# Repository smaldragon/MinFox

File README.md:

# MinFox

**NOTE: As of now, the board is untested, this README will be updated once proper tests with the physical board have taken place**

This is a minimal 65c02 board for prototyping, it provides ROM, RAM, 6 Chip Select lines (S1-S6), and a large jumper header with all the required signals to connect to daughter boards or to breadboards. The goal is to have a dumb, as simple as possible board for testing peripherals connected to a 65c02 bus.

All components are through hole, as to allow for an easier soldering experience and for the installation of sockets for IC reuse.

## Bill of Materials

* wdc65c02 CPU (dip-40)
* 74hc00 Quad Nand Gate (dip-14)
* 74hc138 3-to-8 Decoder (dip-16)
* Standard 62xxx SRAM (dip-28 or dip-32)
* Standard 28cXX EEPROM (dip-28) or 39SF0x0 Flash NOR (dip-32 or PLCC-32)
* Standard 1Mhz Clock Oscillator

* 2x20 Pin Socket (same size as RPi connector)
* 1x3  Pin Socket
* 2x2  Pin Header (+ 2 Jumpers)
* DIP-12 Switch
* Small 6-Pin Power Slide Switch
* USB-B Connector (power)

* 3xPush Buttons
* 1x470Ω
* 3x1KΩ
* 1x10µF Polarized Capacitor
* 8x0.1µF Capacitor
* 2x9pin Resistor Networks

The location and values of all components are also described in the board silk screen.

## Change Log

Board revisions  follow a `v$number$letter` naming scheme, the number symbolizes a board with new features and incompatibilities, while the letter symbolizes fixes and minor tweaks. The current version is **v1a**

### v1a

* Fixed breaking bug with /WR signal
* Added Screw Mounts
* Added Support for DIP-32 RAM and DIP-32/PLCC-32 Flash NOR chips
* Added Jumper for disconnecting clock oscillator
* Added Jumper for gating slot select signals with ø2
* Added dip switch for setting a ROM bank to use
* Added Set Overflow signal to the Connector
* Changed footprint of power slide switch
* Many tweaks to silkscreen

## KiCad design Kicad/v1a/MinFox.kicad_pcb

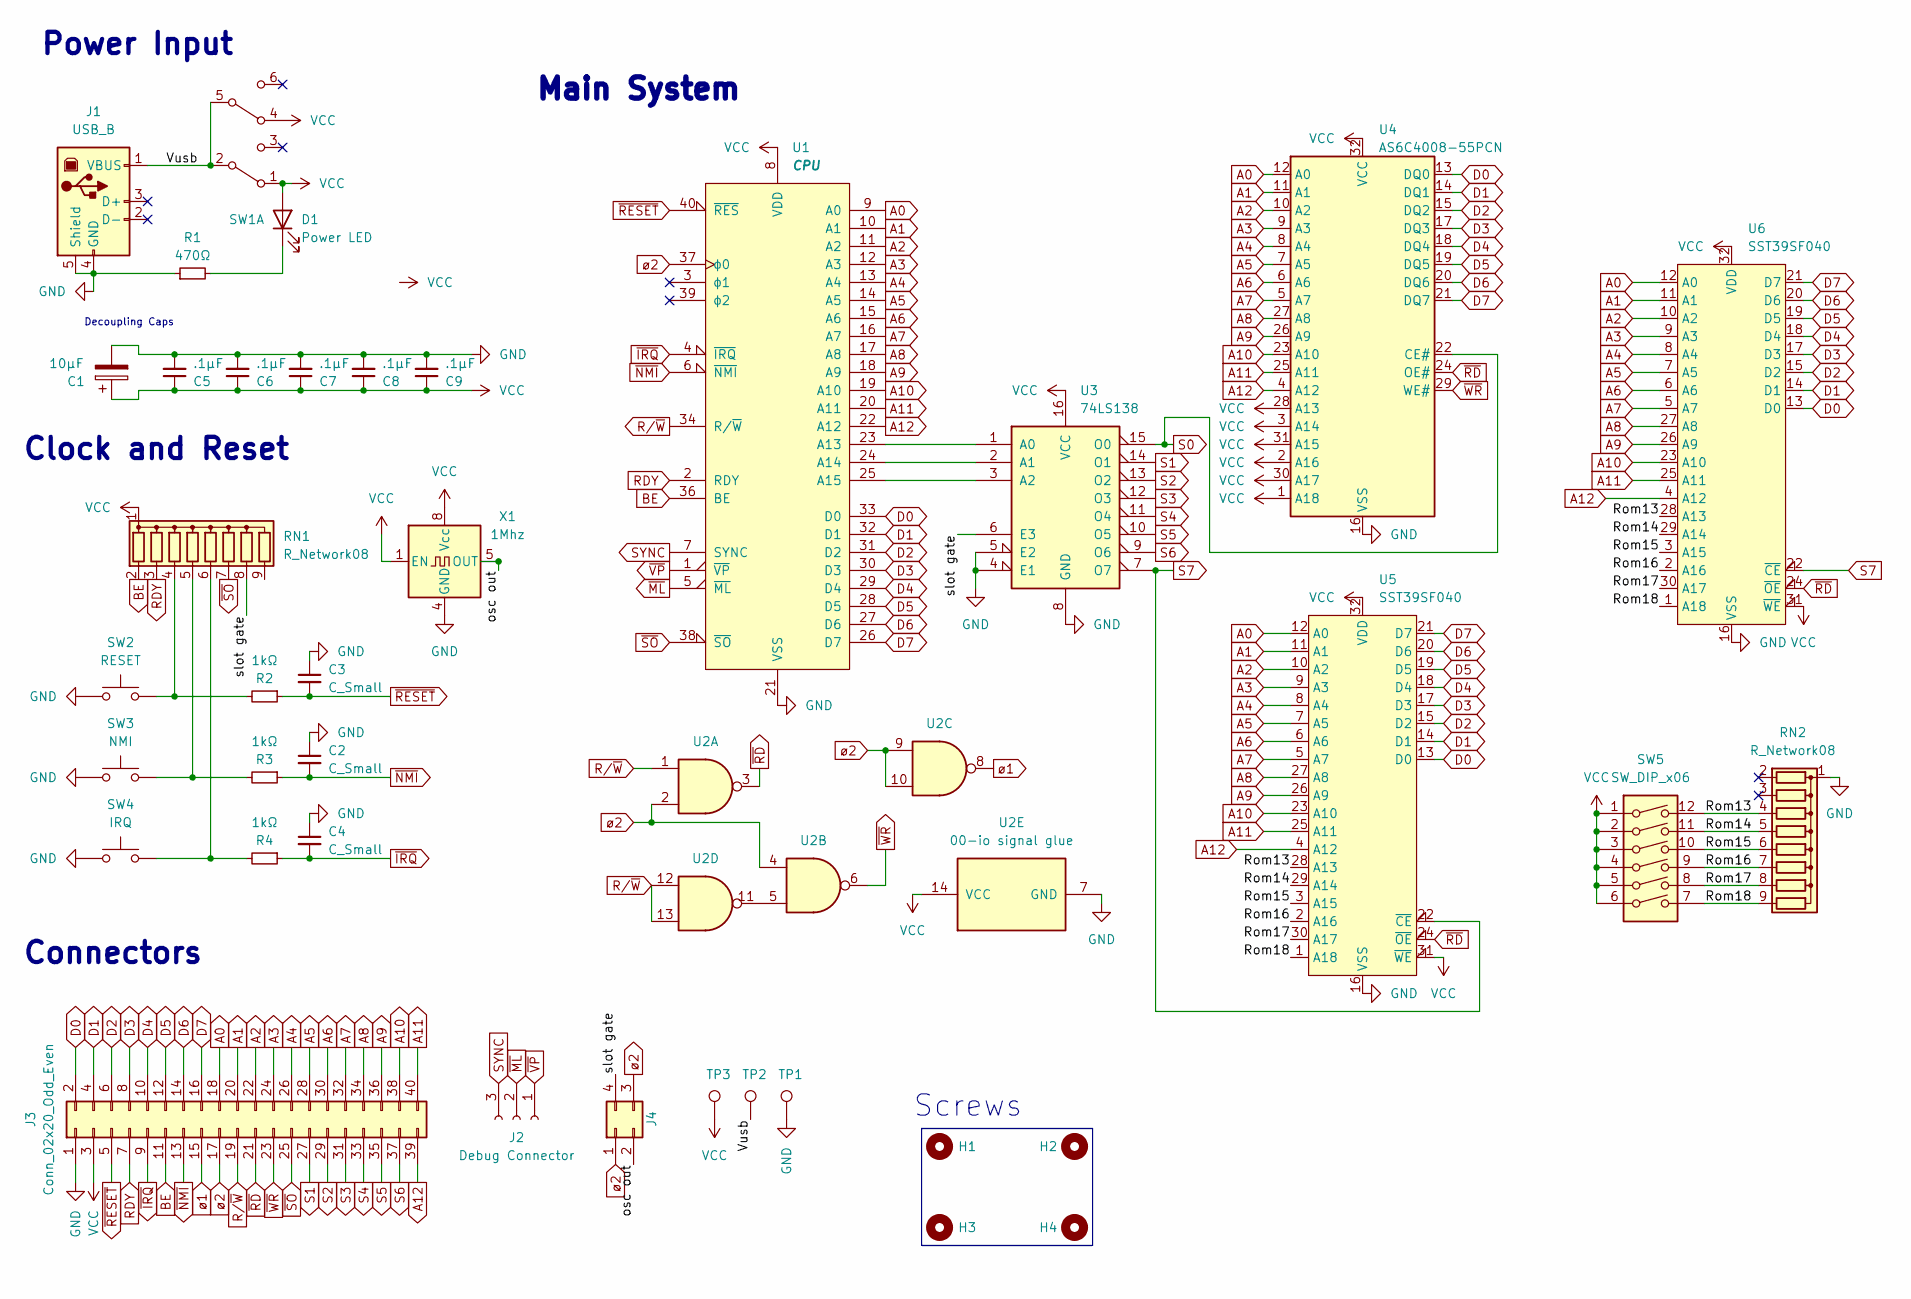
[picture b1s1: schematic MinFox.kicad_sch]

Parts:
C1: 10µF; CP_Radial_D4.0mm_P1.50mm
C2, C3, C4: C_Small; C_Disc_D3.0mm_W1.6mm_P2.50mm
C5, C6, C7, C8, C9: .1µF; C_Disc_D3.0mm_W1.6mm_P2.50mm
D1: Power LED; LED_D5.0mm
H1, H2, H3, H4: MountingHole; MountingHole_3.2mm_M3
J1: USB_B; USB_B_OST_USB-B1HSxx_Horizontal
J2: Debug Connector; PinSocket_1x03_P2.54mm_Vertical
J3: Conn_02x20_Odd_Even; PinSocket_2x20_P2.54mm_Vertical
J4: Conn_02x02_Counter_Clockwise; PinHeader_2x02_P2.54mm_Vertical
R1: 470Ω; R_Axial_DIN0204_L3.6mm_D1.6mm_P7.62mm_Horizontal
R2, R3, R4: 1kΩ; R_Axial_DIN0204_L3.6mm_D1.6mm_P7.62mm_Horizontal
RN1, RN2: R_Network08; R_Array_SIP9
SW1: SW_DPDT_x2; SW_CuK_JS202011AQN_DPDT_Angled
SW2: RESET; SW_PUSH_6mm
SW3: NMI; SW_PUSH_6mm
SW4: IRQ; SW_PUSH_6mm
SW5: SW_DIP_x06; SW_DIP_SPSTx06_Slide_6.7x16.8mm_W7.62mm_P2.54mm_LowProfile
TP1: GND; TestPoint_Pad_D2.0mm
TP2: Vusb; TestPoint_Pad_D2.0mm
TP3: Vcc; TestPoint_Pad_D2.0mm
U1: CPU; DIP-40_W15.24mm_Socket
U2: 00-io signal glue; DIP-14_W7.62mm_Socket
U3: 74LS138; DIP-16_W7.62mm_Socket
U4: AS6C4008-55PCN; DIP-32_W15.24mm_Socket
U5: SST39SF040; DIP-32_W15.24mm_Socket
U6: SST39SF040; PLCC-32_THT-Socket
X1: 1Mhz; Oscillator_DIP-8

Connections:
/Rom13: RN2.4 (R3), SW5.12, U5.28 (A13), U6.28 (A13)
/Rom14: RN2.5 (R4), SW5.11, U5.29 (A14), U6.29 (A14)
/Rom15: RN2.6 (R5), SW5.10, U5.3 (A15), U6.3 (A15)
/Rom16: RN2.7 (R6), SW5.9, U5.2 (A16), U6.2 (A16)
/Rom17: RN2.8 (R7), SW5.8, U5.30 (A17), U6.30 (A17)
/Rom18: RN2.9 (R8), SW5.7, U5.1 (A18), U6.1 (A18)
/Vusb: J1.1 (VBUS), SW1.2 (B), SW1.5 (B), TP2.1
/osc out: J4.2, X1.5 (OUT)
/slot gate: J4.4, RN1.8 (R7), U3.6 (E3)
A0: J3.18, U1.9 (A0), U4.12 (A0), U5.12 (A0), U6.12 (A0)
A1: J3.20, U1.10 (A1), U4.11 (A1), U5.11 (A1), U6.11 (A1)
A2: J3.22, U1.11 (A2), U4.10 (A2), U5.10 (A2), U6.10 (A2)
A3: J3.24, U1.12 (A3), U4.9 (A3), U5.9 (A3), U6.9 (A3)
A4: J3.26, U1.13 (A4), U4.8 (A4), U5.8 (A4), U6.8 (A4)
A5: J3.28, U1.14 (A5), U4.7 (A5), U5.7 (A5), U6.7 (A5)
A6: J3.30, U1.15 (A6), U4.6 (A6), U5.6 (A6), U6.6 (A6)
A7: J3.32, U1.16 (A7), U4.5 (A7), U5.5 (A7), U6.5 (A7)
A8: J3.34, U1.17 (A8), U4.27 (A8), U5.27 (A8), U6.27 (A8)
A9: J3.36, U1.18 (A9), U4.26 (A9), U5.26 (A9), U6.26 (A9)
A10: J3.38, U1.19 (A10), U4.23 (A10), U5.23 (A10), U6.23 (A10)
A11: J3.40, U1.20 (A11), U4.25 (A11), U5.25 (A11), U6.25 (A11)
A12: J3.39, U1.22 (A12), U4.4 (A12), U5.4 (A12), U6.4 (A12)
BE: J3.11, RN1.2 (R1), U1.36 (BE)
D0: J3.2, U1.33 (D0), U4.13 (DQ0), U5.13 (D0), U6.13 (D0)
D1: J3.4, U1.32 (D1), U4.14 (DQ1), U5.14 (D1), U6.14 (D1)
D2: J3.6, U1.31 (D2), U4.15 (DQ2), U5.15 (D2), U6.15 (D2)
D3: J3.8, U1.30 (D3), U4.17 (DQ3), U5.17 (D3), U6.17 (D3)
D4: J3.10, U1.29 (D4), U4.18 (DQ4), U5.18 (D4), U6.18 (D4)
D5: J3.12, U1.28 (D5), U4.19 (DQ5), U5.19 (D5), U6.19 (D5)
D6: J3.14, U1.27 (D6), U4.20 (DQ6), U5.20 (D6), U6.20 (D6)
D7: J3.16, U1.26 (D7), U4.21 (DQ7), U5.21 (D7), U6.21 (D7)
GND: C1.2, C2.1, C3.1, C4.1, C5.2, C6.2, C7.2, C8.2, C9.2, J1.4 (GND), J1.5 (Shield), J3.1, R1.1, RN2.1 (common), SW2.1, SW3.1, SW4.1, TP1.1, U1.21 (VSS), U2.7 (GND), U3.4 (E1), U3.5 (E2), U3.8 (GND), U4.16 (VSS), U5.16 (VSS), U6.16 (VSS), X1.4 (GND)
unnamed: D1.1 (K), R1.2
unnamed: R2.2, RN1.4 (R3), SW2.2
unnamed: R3.2, RN1.5 (R4), SW3.2
unnamed: R4.2, RN1.6 (R5), SW4.2
unnamed: U1.23 (A13), U3.1 (A0)
unnamed: U1.24 (A14), U3.2 (A1)
unnamed: U1.25 (A15), U3.3 (A2)
unnamed: U2.5, U2.11
RDY: J3.7, RN1.3 (R2), U1.2 (RDY)
R/~W: J3.19, U1.34 (R/~W), U2.1, U2.12, U2.13
S0: U3.15 (O0), U4.22 (CE#)
S1: J3.27, U3.14 (O1)
S2: J3.29, U3.13 (O2)
S3: J3.31, U3.12 (O3)
S4: J3.33, U3.11 (O4)
S5: J3.35, U3.10 (O5)
S6: J3.37, U3.9 (O6)
S7: U3.7 (O7), U5.22 (~CE), U6.22 (~CE)
SYNC: J2.3, U1.7 (SYNC)
VCC: C1.1, C5.1, C6.1, C7.1, C8.1, C9.1, D1.2 (A), J3.3, RN1.1 (common), SW1.1 (A), SW1.4 (A), SW5.1, SW5.2, SW5.3, SW5.4, SW5.5, SW5.6, TP3.1, U1.8 (VDD), U2.14 (VCC), U3.16 (VCC), U4.1 (A18), U4.2 (A16), U4.3 (A14), U4.28 (A13), U4.30 (A17), U4.31 (A15), U4.32 (VCC), U5.31 (~WE), U5.32 (VDD), U6.31 (~WE), U6.32 (VDD), X1.1 (EN), X1.8 (Vcc)
~IRQ: C4.2, J3.9, R4.1, U1.4 (~IRQ)
~ML: J2.2, U1.5 (~ML)
~NMI: C2.2, J3.13, R3.1, U1.6 (~NMI)
~RD: J3.21, U2.3, U4.24 (OE#), U5.24 (~OE), U6.24 (~OE)
~RESET: C3.2, J3.5, R2.1, U1.40 (~RES)
~SO: J3.25, RN1.7 (R6), U1.38 (~SO)
~VP: J2.1, U1.1 (~VP)
~WR: J3.23, U2.6, U4.29 (WE#)
ø1: J3.15, U2.8
ø2: J3.17, J4.1, J4.3, U1.37 (ϕ0), U2.2, U2.4, U2.9, U2.10

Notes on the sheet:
Clock and Reset
Main System
Screws
Decoupling Caps
Power Input
Connectors

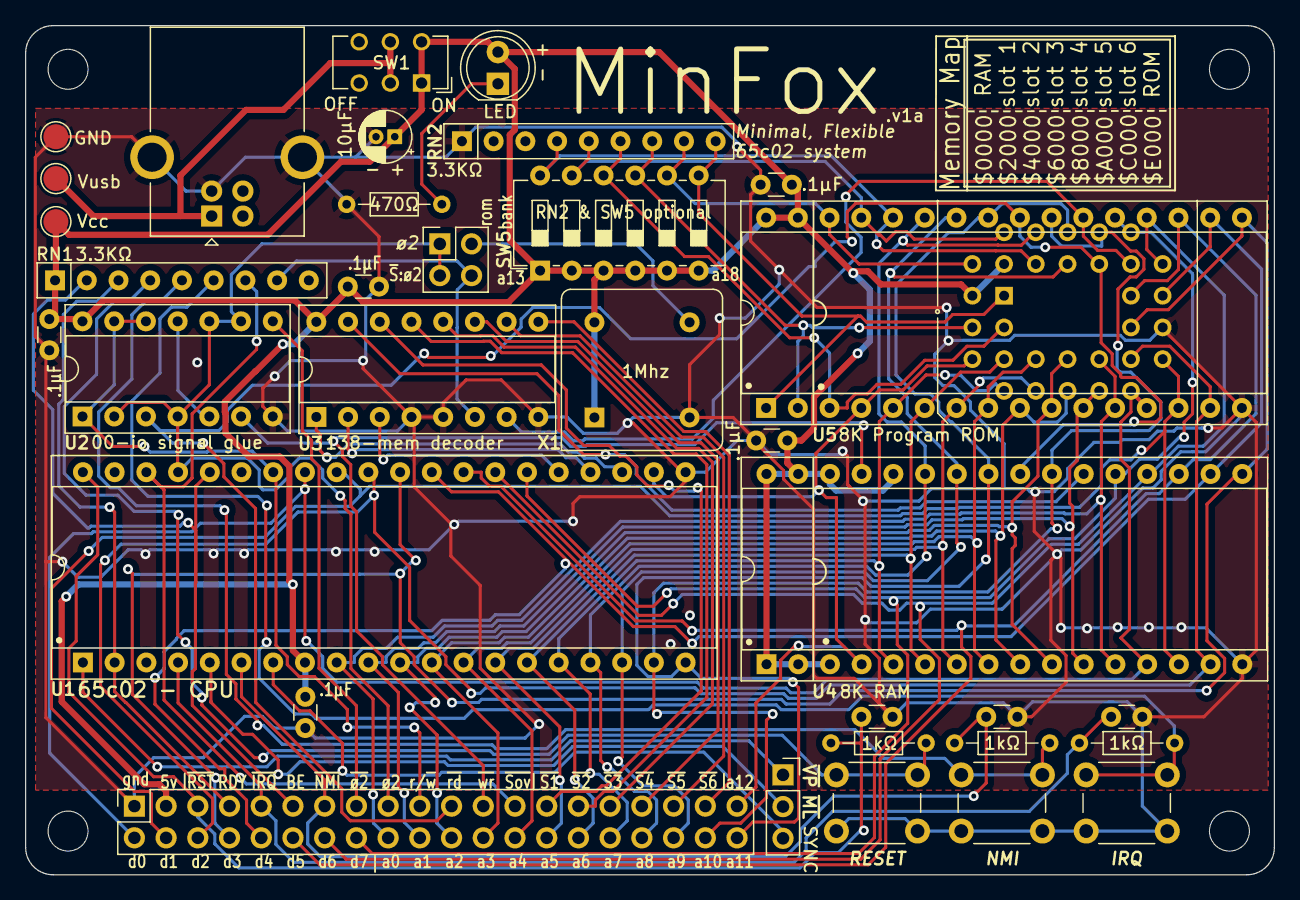
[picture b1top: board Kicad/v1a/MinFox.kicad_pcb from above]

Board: 2 copper layers, 100.0 x 68.0 mm, 39 parts (0 on the bottom side), 62 nets.

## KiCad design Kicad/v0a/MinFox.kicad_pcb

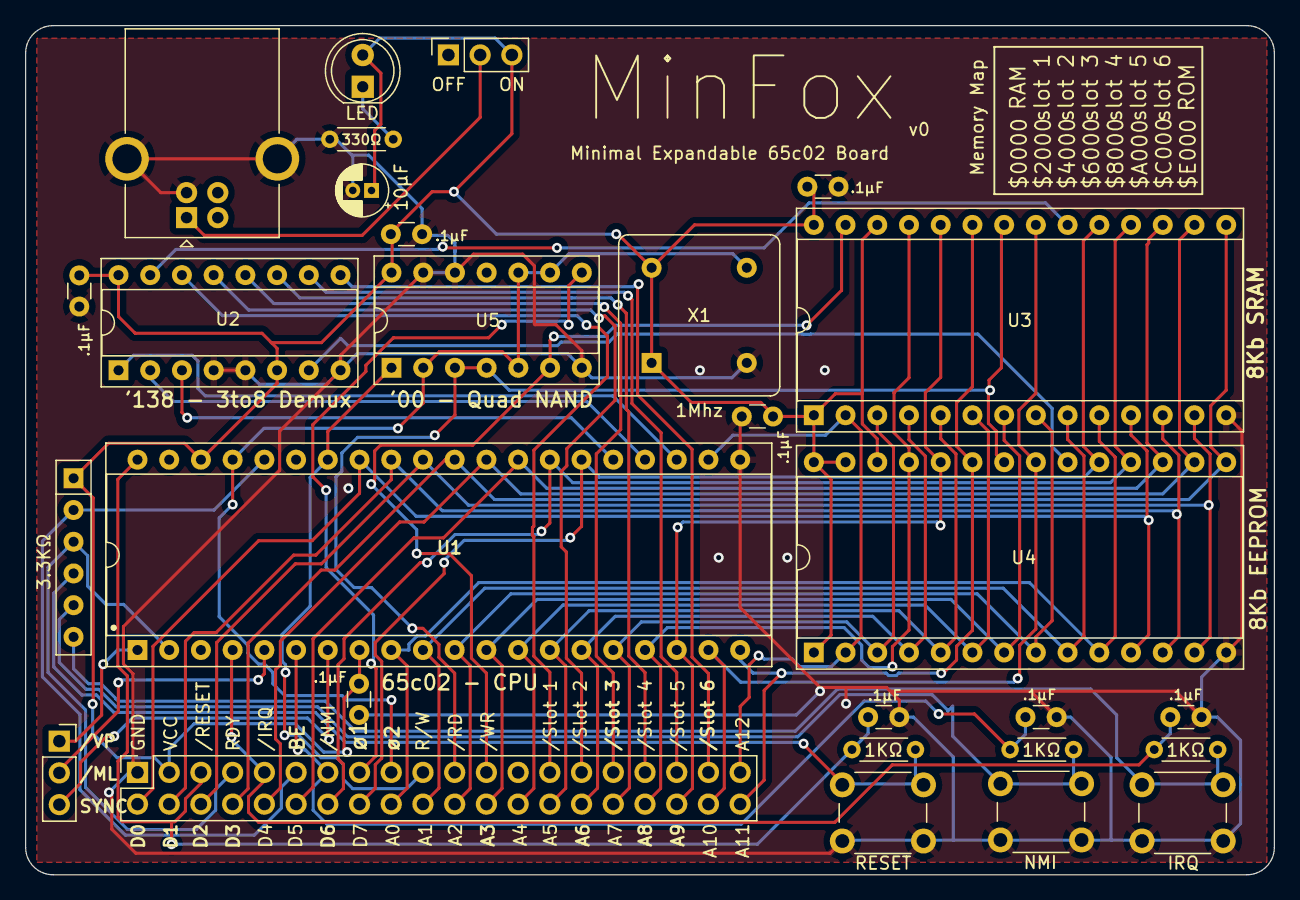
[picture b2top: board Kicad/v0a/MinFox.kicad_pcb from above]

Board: 2 copper layers, 100.0 x 68.0 mm, 28 parts (0 on the bottom side), 52 nets.

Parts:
C1: decoup; CP_Radial_D4.0mm_P1.50mm
C2, C3, C4, C5, C6, C7, C8, C9: C_Small; C_Disc_D3.0mm_W1.6mm_P2.50mm
D1: Power LED; LED_D5.0mm
J1: USB_B; USB_B_OST_USB-B1HSxx_Horizontal
J2: Debug Connector; PinSocket_1x03_P2.54mm_Vertical
J3: Conn_02x20_Odd_Even; PinSocket_2x20_P2.54mm_Vertical
R1: 330Ω; R_Axial_DIN0204_L3.6mm_D1.6mm_P5.08mm_Horizontal
R5, R6, R10: 3.3kΩ; R_Axial_DIN0204_L3.6mm_D1.6mm_P5.08mm_Horizontal
RN1: R_Network05; R_Array_SIP6
SW1: SW_SPDT; PinSocket_1x03_P2.54mm_Vertical
SW2: RESET; SW_PUSH_6mm
SW3: NMI; SW_PUSH_6mm
SW4: IRQ; SW_PUSH_6mm
U1: CPU; DIP-40_W15.24mm_Socket
U2: 74LS138; DIP-16_W7.62mm_Socket
U3: 8Kb SRAM; DIP-28_W15.24mm_Socket
U4: 8Kb EEPROM; DIP-28_W15.24mm_Socket
U5: 74HC00; DIP-14_W7.62mm_Socket
X1: 1Mhz; Oscillator_DIP-8

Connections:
A0: J3.18, U1.9 (A0), U3.10 (A0), U4.10 (A0)
A1: J3.20, U1.10 (A1), U3.9 (A1), U4.9 (A1)
A2: J3.22, U1.11 (A2), U3.8 (A2), U4.8 (A2)
A3: J3.24, U1.12 (A3), U3.7 (A3), U4.7 (A3)
A4: J3.26, U1.13 (A4), U3.6 (A4), U4.6 (A4)
A5: J3.28, U1.14 (A5), U3.5 (A5), U4.5 (A5)
A6: J3.30, U1.15 (A6), U3.4 (A6), U4.4 (A6)
A7: J3.32, U1.16 (A7), U3.3 (A7), U4.3 (A7)
A8: J3.34, U1.17 (A8), U3.25 (A8), U4.25 (A8)
A9: J3.36, U1.18 (A9), U3.24 (A9), U4.24 (A9)
A10: J3.38, U1.19 (A10), U3.21 (A10), U4.21 (A10)
A11: J3.40, U1.20 (A11), U3.23 (A11), U4.23 (A11)
A12: J3.39, U1.22 (A12), U3.2 (A12), U4.2 (A12)
BE: J3.11, RN1.2 (R1), U1.36 (BE)
D0: J3.2, U1.33 (D0), U3.11 (Q0), U4.11 (D0)
D1: J3.4, U1.32 (D1), U3.12 (Q1), U4.12 (D1)
D2: J3.6, U1.31 (D2), U3.13 (Q2), U4.13 (D2)
D3: J3.8, U1.30 (D3), U3.15 (Q3), U4.15 (D3)
D4: J3.10, U1.29 (D4), U3.16 (Q4), U4.16 (D4)
D5: J3.12, U1.28 (D5), U3.17 (Q5), U4.17 (D5)
D6: J3.14, U1.27 (D6), U3.18 (Q6), U4.18 (D6)
D7: J3.16, U1.26 (D7), U3.19 (Q7), U4.19 (D7)
GND: C1.2, C2.1, C3.1, C4.1, C5.2, C6.2, C7.2, C8.2, C9.2, J1.4 (GND), J1.5 (Shield), J3.1, R1.1, SW2.1, SW3.1, SW4.1, U1.21 (VSS), U2.4 (E1), U2.5 (E2), U2.8 (GND), U3.14 (GND), U4.14 (GND), U5.7 (GND), U5.12, U5.13, X1.4 (GND)
unnamed: D1.1 (K), R1.2
unnamed: J1.1 (VBUS), SW1.2 (B)
unnamed: R5.2, RN1.4 (R3), SW2.2
unnamed: R6.2, RN1.5 (R4), SW3.2
unnamed: R10.2, RN1.6 (R5), SW4.2
unnamed: U1.23 (A13), U2.1 (A0)
unnamed: U1.24 (A14), U2.2 (A1)
unnamed: U1.25 (A15), U2.3 (A2)
RDY: J3.7, RN1.3 (R2), U1.2 (RDY)
R/~W: J3.19, U1.34 (R/~W), U5.1
S0: U2.15 (O0), U3.20 (~CS)
S1: J3.27, U2.14 (O1)
S2: J3.29, U2.13 (O2)
S3: J3.31, U2.12 (O3)
S4: J3.33, U2.11 (O4)
S5: J3.35, U2.10 (O5)
S6: J3.37, U2.9 (O6)
S7: U2.7 (O7), U4.20 (~CS)
SYNC: J2.3, U1.7 (SYNC)
VCC: C1.1, C5.1, C6.1, C7.1, C8.1, C9.1, D1.2 (A), J3.3, RN1.1 (common), SW1.3 (C), U1.8 (VDD), U1.38 (~SO), U2.6 (E3), U2.16 (VCC), U3.1 (A14), U3.26 (A13), U3.28 (VCC), U4.1 (A14), U4.26 (A13), U4.27 (~WE), U4.28 (VCC), U5.14 (VCC), X1.1 (EN), X1.8 (Vcc)
~IRQ: C4.2, J3.9, R10.1, U1.4 (~IRQ)
~ML: J2.2, U1.5 (~ML)
~NMI: C2.2, J3.13, R6.1, U1.6 (~NMI)
~RD: J3.21, U3.22 (~OE), U4.22 (~OE), U5.3, U5.4
~RESET: C3.2, J3.5, R5.1, U1.40 (~RES)
~VP: J2.1, U1.1 (~VP)
~WR: J3.23, U3.27 (~WE), U5.6
ø1: J3.15, U5.8
ø2: J3.17, U1.37 (ϕ0), U5.2, U5.5, U5.9, U5.10, X1.5 (OUT)
